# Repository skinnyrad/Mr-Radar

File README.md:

# Mr Radar
Mr. Radar is a port security evading, discovery device used to detect network switches connected to lone network ports. In addition, it has the ability to detect if Power over Ethernet (PoE) is present and whether the PoE being provide is Mode A or Mode B in nature. An understanding of the functionality of Mr. Radar can be found here: https://skinnyrd.com/mr-radar-layer-1-recon/

Mr. Radar has the following indicators that appear on the Trinket M0.
- Small Green LED: Mr. Radar is ON. LED is located to the left of the µUSB connector.
- Large Green LED: Mr. Radar has discovered a network device. LED is the Dotstar in the center.
- Large Orange LED: Mr. Radar has discovered a network device that can only support 10/100 Mbits/s. LED is the Dotstar in the center.
- Small Rapid Blinking Red LED: Mr. Radar has detected PoE in a Mode A configuration. LED is located to the right of the µUSB connector.
- Small Slowly Blinking Red LED: Mr. Radar has detected PoE in a Mode B configuration. LED is located to the right of the µUSB connector.

## Github File Structure
The hardware folder contains the KiCad project files for Mr. Radar. The MrRadar_firmware folder contains the .ino file for the Arduino IDE. These files will be used to program the Trinket M0 which controls Mr. Radar.

## Schematic
If you don't want to bother with KiCad and just want to make the board from scratch or want to use another microcontroller, the schematic below will help.

## Bill of Materials
- J1: [RJ-45 Connector](https://www.digikey.com/short/mw80n14h)
- R1: 100kΩ 1/4W
- R2: 100kΩ 1/4W
- R3: 10kΩ 1/4W
- R4: 10kΩ 1/4W
- R5: 10kΩ 1/4W
- R6: 3.3kΩ 1/4W
- R7: 10kΩ 1/4W
- R8: 100kΩ 1/4W
- R9: 100kΩ 1/4W
- U1: [Trinket M0](https://www.adafruit.com/product/3500)
- SW1: [SPST Switch](https://www.digikey.com/short/q5dbrt7p)
- BT1: [Battery Pack](https://www.digikey.com/short/m8dprrz4)
- 2 Machine Screws: [#2-56 Thread Size, 1/4 in Lg, 18-8](https://www.grainger.com/product/GRAINGER-APPROVED-Machine-Screw-2-56-Thread-1ZB23?searchQuery=1ZB23&searchBar=true&tier=Not+Applicable)
- 2 Hex Nuts: [Plain, 18-8, Stainless Steel, #2-56 Thread](https://www.grainger.com/product/GRAINGER-APPROVED-Hex-Nut-Plain-1WA81?searchQuery=1WA81&searchBar=true&tier=Not+Applicable)

## Tips for construction
- When loading the code for the Trinket M0, ensure you have setup the Trinket according to the [Adafruit tutorial](https://learn.adafruit.com/adafruit-trinket-m0-circuitpython-arduino). Use the Arduino IDE setup procedures.
- The battery pack goes on the bottom of the board. You'll need to solder everything on top first and then clip all the excess wire pieces before affixing the battery pack.

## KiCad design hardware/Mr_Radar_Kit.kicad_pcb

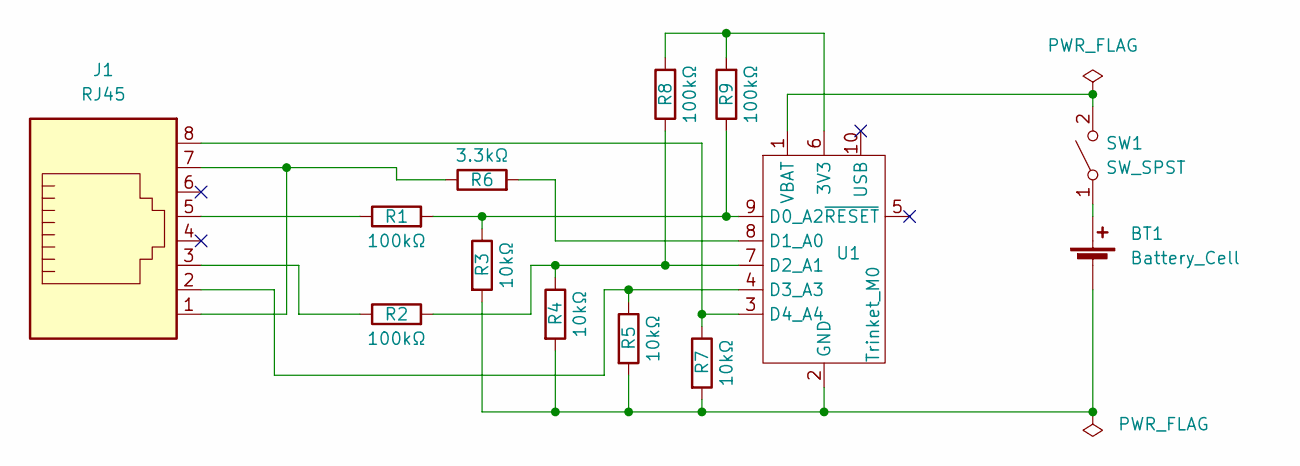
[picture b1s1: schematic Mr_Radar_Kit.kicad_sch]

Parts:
BT1: Battery_Cell; AAA_Keystone_2479
J1: RJ45; RJ45_RJSSE-5080
R1, R2, R8, R9: 100kΩ; R_Axial_DIN0207_L6.3mm_D2.5mm_P10.16mm_Horizontal
R3, R4, R5, R7: 10kΩ; R_Axial_DIN0207_L6.3mm_D2.5mm_P10.16mm_Horizontal
R6: 3.3kΩ; R_Axial_DIN0207_L6.3mm_D2.5mm_P10.16mm_Horizontal
SW1: SW_SPST; SW_DIP_SPSTx01_Slide_9.78x4.72mm_W7.62mm_P2.54mm
U1: Trinket_M0; Trinket M0

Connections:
unnamed: BT1.1 (+), SW1.1 (A)
unnamed: BT1.2 (-), R3.2, R4.2, R5.2, R7.2, U1.2 (GND)
unnamed: J1.1, J1.7, R6.1
unnamed: J1.2, R5.1, U1.4 (D3_A3)
unnamed: J1.3, R2.1
unnamed: J1.5, R1.1
unnamed: J1.8, R7.1, U1.3 (D4_A4)
unnamed: R1.2, R3.1, R9.1, U1.9 (D0_A2)
unnamed: R2.2, R4.1, R8.1, U1.7 (D2_A1)
unnamed: R6.2, U1.8 (D1_A0)
unnamed: SW1.2 (B), U1.1 (VBAT)
unnamed: R8.2, R9.2, U1.6 (3V3)

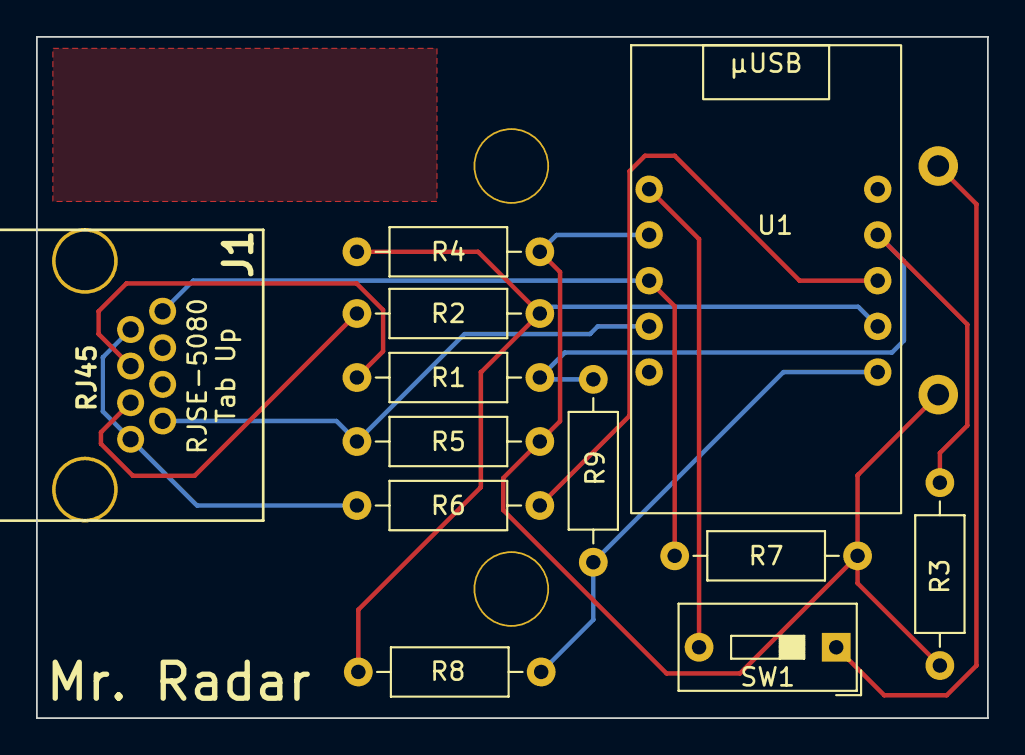
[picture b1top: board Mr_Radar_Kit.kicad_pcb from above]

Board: 2 copper layers, 52.8 x 37.8 mm, 13 parts (1 on the bottom side), 12 nets.

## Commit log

2023-01-03 initial upload
2023-01-16 Creating the read me file
2023-01-16 Update README.md
    Updated with blog post link
2023-01-16 Update README.md
    Added a schematic to the README
2023-01-17 Update README.md
    Updated description to detail how Mr. Radar works.
2023-01-17 Update MrRadar_firmware.ino
    Widened the Mode A and Mode B detection criteria
2023-01-23 chore:update Markdown
2023-01-23 chore:remove repetitive .zip
2023-02-13 Update README.md
    Updated BOM
